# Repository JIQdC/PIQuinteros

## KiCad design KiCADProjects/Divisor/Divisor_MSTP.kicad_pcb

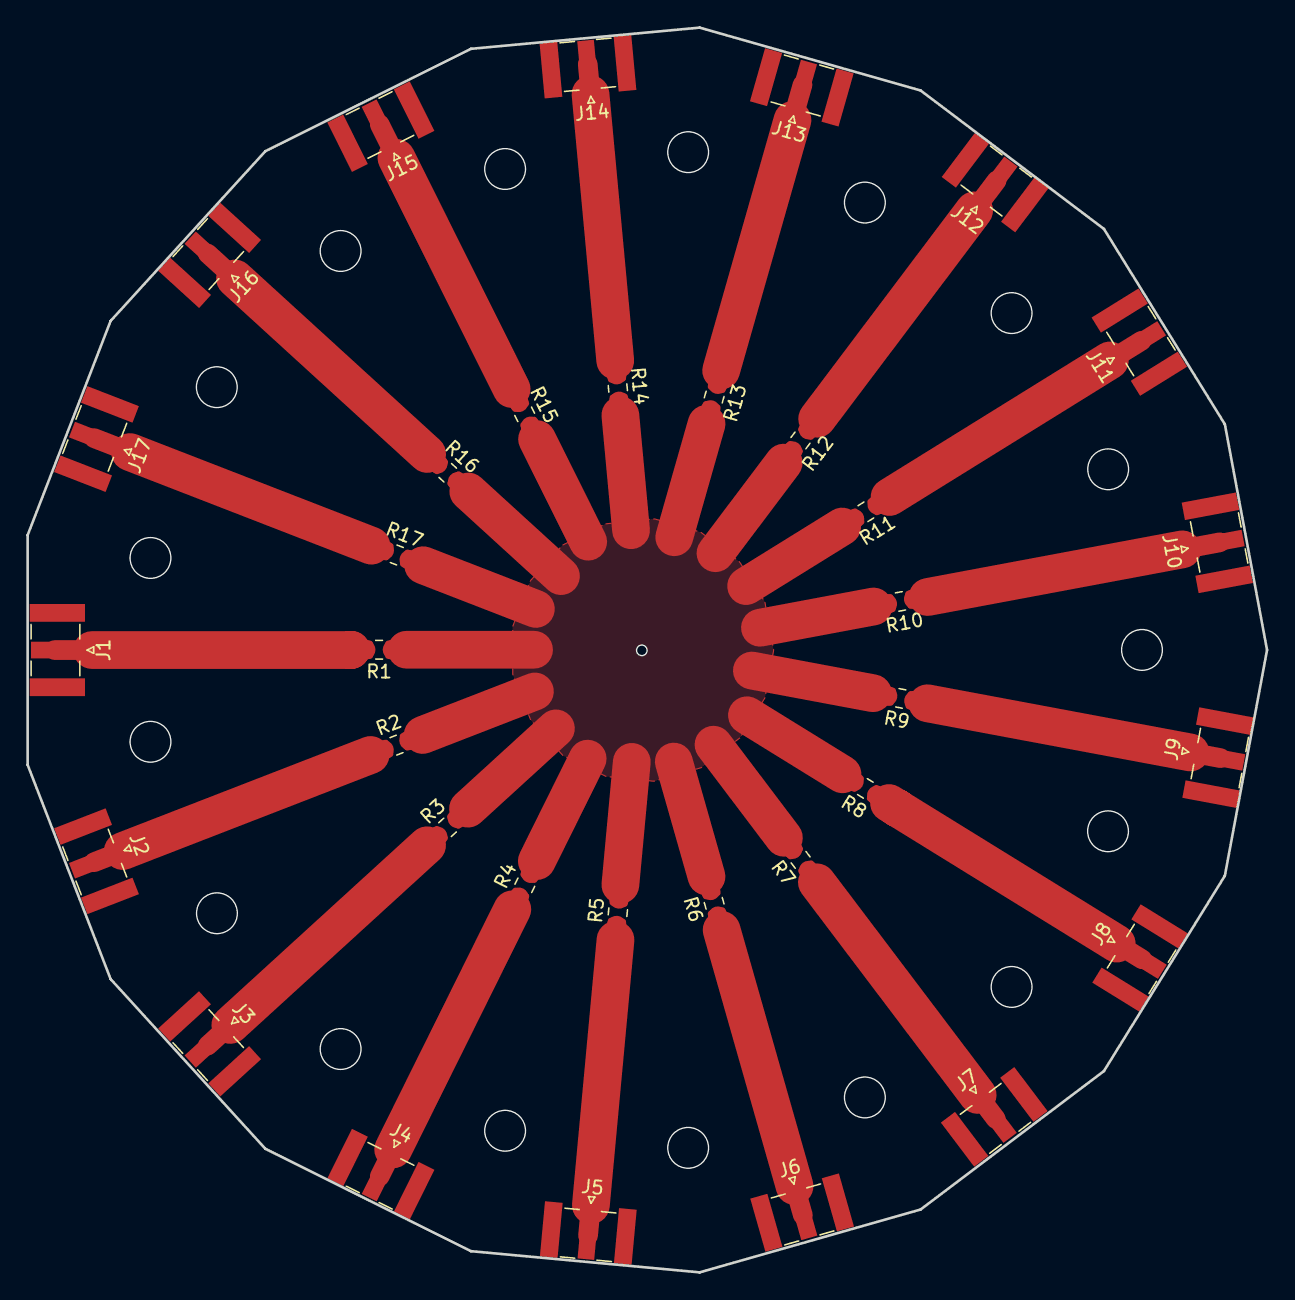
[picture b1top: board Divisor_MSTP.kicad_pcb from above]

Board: 2 copper layers, 94.2 x 94.6 mm, 34 parts (0 on the bottom side), 19 nets.

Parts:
J1, J2, J3, J4, J5, J6, J7, J8, J9, J10, J11, J12, J13, J14, J15, J16, J17: SMA_Female; SMA_Samtec_SMA-J-P-X-ST-EM1_EdgeMount
R1, R2, R3, R4, R5, R6, R7, R8, R9, R10, R11, R12, R13, R14, R15, R16, R17: 43; R_0805_2012Metric_Pad1.15x1.40mm_HandSolder

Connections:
GND: J1.2, J2.2, J3.2, J4.2, J5.2, J6.2, J7.2, J8.2, J9.2, J10.2, J11.2, J12.2, J13.2, J14.2, J15.2, J16.2, J17.2
unnamed: J1.1, R1.2
unnamed: J2.1, R2.1
unnamed: J3.1, R3.1
unnamed: J4.1, R4.1
unnamed: J5.1, R5.1
unnamed: J6.1, R6.1
unnamed: J7.1, R7.1
unnamed: J8.1, R8.1
unnamed: J9.1, R9.1
unnamed: J10.1, R10.1
unnamed: J11.1, R11.1
unnamed: J12.1, R12.1
unnamed: J13.1, R13.1
unnamed: J14.1, R14.1
unnamed: J15.1, R15.1
unnamed: J16.1, R16.1
unnamed: J17.1, R17.1
unnamed: R1.1, R2.2, R3.2, R4.2, R5.2, R6.2, R7.2, R8.2, R9.2, R10.2, R11.2, R12.2, R13.2, R14.2, R15.2, R16.2, R17.2

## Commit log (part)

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2019-08-12 Nueva frec. central, corrección de acumulador, def. de longitud inicial.
2019-08-14 Reorganización de archivos. Creé RectArray.py para las funciones de implementación de array rectangular.
2019-08-14 Primera versión del simulador de array rectangular. En el caso lineal (Nx1) se obtienen resultados parecidos a la versión anterior. Hay que eliminar la aproximación de punto lejano, y reemplazarla po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
2019-08-15 Modificación de la fórmula de cálculo de distancia en el array rectangular, modelando el frente de onda como un plano y tomando distancia punto plano. Agregué ArraySimulatorOld.py para comparar desem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
2019-09-09 Definición de dimensiones del arreglo (4x4) y dirección de arribo (theta = 30^o y phi = 15^o). Redefinición del formato en el que se entregan los retardos en la función calcTimeDelay, para posibilita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
2019-09-27 Creación de carpeta /VHDL para guardar los fuentes que vaya desarrollando. Agregué archivos fuentes para la simulación de transacciones de bus AXI, utilizando simuladores de CLOCK y RST_N. Script TCL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
2019-10-21 Primeras versiones de adc_model.vhd y test_adc_model.vhd, que AÚN no funcionan, orientadas a modelar el funcionamiento de uno de los canales del ADC que usaremos.
2019-10-28 Modificación del modelo de ADC para generar un flag cuando se bufferea la entrada. Implementación de un contador de N bits que se actualiza con el flag mencionado. Testbench de prueba.
2019-10-28 one-/zero-word toggle, descrito en el datasheet del ADC
2019-10-29 Implementación de un wrapper con casi todas las secuencias de prueba posibles del AD9249. Testbench. Modificación del contador de N bits para tomar valor on reset como entrada. Corrección general de 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
2019-10-29 TCL para recrear el proyecto usado para probar el modelo del ADC
2019-11-11 Wrapper y testbench del módulo DDR
2019-11-11 Deserializador con arquitectura simplificada, y testbench de ADC + DDR + deserializador.
2019-11-11 Corrección del deserializador para arquitectura sincrónica.
2019-11-16 Control de pines de FPGA mediante registros y bus AXI
2019-11-16 Módulo de interfaz entre SPI del PS y SPI 3-wire del ADC
2019-11-19 Agregado de puerto de salida para controlar TP8
2019-11-29 Modificación de tiempo de simulación para permitir simulaciones más largas (10 s)
2019-11-29 Diagrama en bloques del proyecto.
2019-12-20 Módulo negador de señal para su uso en diagramas de bloque (no está como IP en Vivado)
2019-12-20 Módulos de implementación y prueba de interfaz FIFO-AXI, para el sistema de control del ADC
2019-12-20 Diagrama en bloques del módulo de control del ADC, con interfaz AXI para conectar a la PS.
2019-12-20 Modificación de headers, nombres y fechas.
2020-02-13 Modificación del módulo de control de ADC para controlar el flujo de datos entre el deserializador y la FIFO. Modificación de mapa de memoria.
2020-02-29 Actualización de diseños en bloque
2020-02-29 Versión de módulos que se utilizaron en prueba exitosa de interfaz AXI con recursos de debug sintetizados en la FPGA
2020-02-29 Diagrama en bloques usado en prueba exitosa de interfaz AXI con recursos de debug sintetizados en la FPGA
2020-02-29 Programas reg_writer y reg_reader para lectura manual de registros
2020-03-07 Generación de reset por interfaz AXI
2020-03-13 Corrección de listas de sensitividad de procesos
2020-03-13 Modificación de módulo para control de pines, y módulos de prueba
2020-03-13 Modificación para incluir registros de control de módulo pin_control
2020-03-13 Funciones de encendido y apagado del regulador de alimentación de la FPGA, y de configuración del potenciómetro
2020-03-17 Instanciación de BUFGMUX para el multiplexado de clock
2020-03-20 Corrección de encabezados
2020-03-20 Programa para leer N muestras y escribirlas a un archivo.
2020-05-13 Versión 1.0 del divisor de potencia resistivo 1x16
2020-05-13 Esquemático versión 1.0
2020-05-25 Reorganización de archivos. Comienzo de implementación de server. Makefile
2020-05-25 Rev 3
2020-05-26 Versión con comunicación y mecanismos de cierre funcionando OK
2020-05-28 Notebook para análisis de datos capturados en server
2020-05-28 Mecanismos de captura y disparo. Escritura de archivos en server. Correcciones generales
2020-05-28 Implementación de chFile y lista de chFile para separar datos que vienen de cada canal
2020-05-29 Parseo de parámetros de inicio de cliente usando archivos de configuración
2020-06-02 Versión final
2020-06-02 Eliminación de notebook
2020-06-04 Modificación de mecanismos de copia en Cl_Queue_Put/Get. sem_post de server->sem_threads en closeConnection()
2020-06-09 Minor changes
2020-06-10 Actualización de lógica de deserializer a partir de medición de señales de salida de SelectIO
2020-06-10 Señal para testeo de canal bidireccional SPI + revisiones generales
2020-06-12 Adaptación de proyecto redes a sistema de adquisición
2020-06-12 Modificación de ancho de lectura de FIFO, de 14 a 28 bits
2020-06-12 Módulo de validación de bus AXI
2020-07-10 Relocalización de archivos para prueba
2020-07-20 Corrección en mensaje de error por argumentos
2020-07-20 Corrección en tamaño de memoria allocada para paquete a leer
2020-07-20 Programa simplificado de lectura de datos de FIFO
2020-07-20 Pruebas de validación AXI
2020-07-20 Divisor de clock
2020-07-20 Frecuencímetro (contador de pulsos).
2020-07-22 Modificaciones menores
2020-07-22 Modificaciones en lógica de cierre de threads, nuevo mecanismo de disparo noDelay, otras menores. Funciones de reset para FIFO y debug
2020-07-22 Programa para pruebas de validación de funcionamiento de bus AXI
2020-07-22 Reorganización de direcciones de memoria. Nombres de registros
2020-07-24 Corrección de lógica de configuración para adaptarse a solamente escritura disponible.
2020-07-28 Agregado soporte para leer Prog Full flag y Read Data Count en el registro de FIFO flags
2020-07-28 Simplificación de lógica de debug control
2020-07-28 Configuración mínima para funcionamiento de PS en SistAdq
2020-07-28 Diagrama en bloques para funcionamiento de un canal de ADC
2020-07-28 Archivo innecesario
2020-07-28 Borrado archivo binario SistAdq
2020-07-28 Borrado makefile
2020-08-11 Revisión 1.1 de PCBs
2020-08-18 MSTP no tiene plano de tierra!
2020-09-06 Reubicación
2020-09-06 Modificación de software lado cliente para transmitir en TCP, UDP o a archivo
2020-09-06 Implementación de servidor TCP y UDP para correr fuera de CIAA
2020-09-12 Modificaciones menores de programas de server
2020-09-16 Funciones y scripts para control de parametros especificos del ADC via SPI
2020-09-16 Correccion para forzar al daemon PTPD que corre sobre CIAA, a que se ejecute como esclavo
2020-09-16 Implementacion de funciones de uso general. Cambio en almacenamiento de timestamp. Lectura por flag prog_full. Parametros para control de modulo de debug y de divisor de clock antes de capturar.
2020-09-16 Index
2020-09-22 Cambios menores
2020-09-22 Interfaz para graficar resultados
2020-09-25 Modulo de control AXI para IODELAYs
2020-09-25 Agregado de registro adicional para latchear el vector del registro de desplazamiento. Modificacion de logica de generacion de d_valid para su sincronismo con falling edge de la señal de frame.
2020-09-29 Remoción de scripts obsoletos
2020-09-29 Función para convertir enteros a base arbitraria
2020-09-29 Funciones de control y calibracion de IDELAYs
2020-09-29 Ubicacion de almacenamiento de capturas
2020-09-29 Adquisición de muestras a bordo de CIAA
2020-09-30 Reordenamiento de puertos y parámetros Xilinx
2020-09-30 Módulo de recepción de señales ADC
2020-09-30 Modificación lógica de wr_clk y wr_en hacia FIFO
2020-10-05 Parametrizacion de duracion de encendido de LED indicador de reset. Agregado de señales de deteccion de ADC.
2020-10-08 Modificaciones para implementacion de 16 canales
2020-10-08 Primera implementacion de 16 canales
2020-10-08 Añadido de señales de lockeo sobre FCOs
2020-10-10 Primera implementación con 16 canales
2020-10-10 Actualización frecuencia de blink
2020-10-10 Correccion registro salida FIFO. Añadido registros prog_full y debug_enable
2020-10-10 Soporte para debug_enable global
2020-10-13 Nombres de defines y revisión para x16
2020-10-13 Rutina de startup con deteccion de placa y señales ADC
2020-10-17 Bug en asignación de registro de delay_frame_ld de salida
2020-10-18 Reorganizacion de /src. Adaptacion a 16 canales. Prueba de delay
2020-10-18 Formatting
2020-10-18 Adaptacion a 16 canales. Utilizacion de union para escribir en uint32_t y leer en uint16_t
2020-10-18 Formatting and minor changes
2020-10-20 Reorganizacion de funciones para control de input delays. Rutina de calibracion automatica de input delays.
2020-10-20 Error en inicializacion de punteros multiPtr
2020-10-20 Agregado de rutina de calibracion de input delays a script de startup
2020-10-21 Bugs
2020-10-24 Adaptacion de funciones de server a 16 canales.
2020-10-24 Modificación para 16 canales
2020-10-24 Funciones de control para downsampler
2020-10-26 Reorganizacion de repositorio. Agregado de IP cores personalizados y archivos de instanciacion .xcix. Redefinicion para instanciar un solo IDELAYCTRL. Limpieza de archivos no utilizados.
2020-10-26 Changes for single delay locked signal
2020-11-12 Modificacion de configuracion inicial de ADC: encendido de terminacion diferencial de 100 ohm
2020-11-12 Correccion de entrada/salidas de FIFO, y estado inicial de registros
2020-11-12 Agregado de registro adicional en debug_control para relajar timing
2020-11-12 Versión utilizada para fabricación de desfasadores
2020-11-17 Constraints para sistema de adquisición de 16 canales. Herramientas para generación de VHDL y constraints
2020-11-20 Added support for external trigger. Tied counter enable to debug enable
2020-11-20 Single channel acquisition system
2020-11-23 Archivos FPGA en primera entrega informe PI
2020-11-23 Archivos software en primera entrega informe PI
2020-12-01 Agregado script para recrear proyecto sistadq_16
2022-02-27 Add clock group async constraints
2022-03-23 Primeras pruebas de preprocesamiento
2022-09-21 Cambié clocks para hacer preprocesamiento a 260 MHz. Incorporé un sincronizador de pulsos para el CDC de 455/7 a 260. Cambié el frame_clk_wiz por un nuevo clk_wiz porque estaba lockeado
2022-10-12 Incorporación del preprocesamiento. Un solo beam por ahora
2022-10-13 Incorporé el filtro final de cada beam
2022-10-13 Modificación de CHDATA_SIZE, incorporación del VHDL de CRC32, no implementado aún en el sistema
2022-10-15 Agregué un clock post processing ligado al segundo registro del eight_register_block
2022-10-16 Add suggested extensions and formatting rules
2022-10-16 IPs ahora en src/hdl/ip. Actualicé el tcl del proyecto
2022-10-16 Add FIFO input mux with control from 8-reg block
2022-10-16 Update Vivado project, fix some bugs
2022-10-17 Adaptación del proceso de calibración en el startup con el nuevo fifo_input_mux
2022-10-17 Remove clock async constraints, add CDC handling mechanisms
2022-10-19 Eliminated core containers for IPs. Fixed sim errors. WWorking .do files for simulation
2022-10-21 Nuevas entradas al fifo_input_data_mux para debug
2022-10-21 Deshabilite los MARK_DEBUG y revertí el cambio en el serder
2022-10-22 Fix tready. Update de ips
2022-10-24 Simu del sistema completo en /Fpga/sim/test_deser
2022-10-24 Aumenté la decimación del ch_filter a 125. Puse el ADC en modo complemento a 2. Seteo el testpattern a off después de la calibracion.
2022-10-25 Settée el complex_gain a 0 para testear. Cambié la entrada de debug al fifo_mux, ahora entra desde el data_mux
2022-10-26 Fix constraint paths
2022-10-27 Mejorar aumento de resolución en phase increment
2022-10-27 Fix de addrs. Fix de timing agregando FFs a la entrada del deser
2022-10-28 Fix timing. Make local oscillator programmable. Removed downsampler setup from sw
2022-10-31 Begin big refactoring. Make all connections
2022-11-01 Fix interconexiones. Fix false paths en constraints. Implementar preprocesamiento sin optimizaciones
2022-11-01 Finish rearranging modules after splitting adc_receiver and data_handler
2022-11-01 Refactor debug control module
2022-11-01 Fix constraint file
2022-11-01 Fix calibración. Actualizar tcl
2022-11-02 Begin optimizations. Create modules to handle time multiplexing in new beam_handler_bd
2022-11-04 Arreglar preproc con 5 beams! Cambiar hold_data_valid y beam_osc_mux por beam_mux_fsm. Incorporar uso de tuser. Desarrollar módulo axi_joiner
